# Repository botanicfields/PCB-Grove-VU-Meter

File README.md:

# PCB-Grove-VU-Meter
VU Meters into the Grove of M5

# オーディオレベルメーター用Grove(M5)接続基板
　ステレオオーディオ信号を、レベルメーター用のアナログ電圧信号に変換するプリント基板です。アナログ信号2本とM5Stack用の5V電源を、Groveコネクタから出力します。M5StackのLCDにVUメーターのように表示するサンプルプログラムを用意しています。

### サンプルプログラムの動作不良について
(2023/5/6) BF-037.inoは、以下の環境でコンパイルできました。しかしばがら、ADCによるオーディオ信号の取り込みが安定せず、使用に耐えない状況です。
- Arduino IDE 2.1.0
- Boards Manager:  
M5Stack by M5Stack official 2.0.7
- Library:  
M5Stack by M5Stack 0.4.3  
M5GFX 0.1.6

[内容物]  

動作例（YouTube）: [Audio level (VU/McIntosh) meters into the Grove of M5Stack](https://youtu.be/Pwd8X57_v_Q)

委託販売（スイッチサイエンス）:  [オーディオレベルメーター用Grove(M5)接続基板](https://www.switch-science.com/catalog/7947/)

## 安全上の注意事項
- 異常の場合、躊躇なくDCプラグを抜いてください（基板上のレギュレータ(U3)が触れないぐらい発熱しているなど）。その上で原因を取り除いてください。
- Groveへの5V出力は、必要な場合以外は、ジャンパピンJP3で切り離してください。特に電源が3.3Vの装置に5Vを供給すると焼損など事故の原因となります。
- 本基板からの5VとM5Stack側からの5Vは共存できません。僅かな電圧差から大電流が流れ、素子の発熱による火傷や、M5Stackの故障の原因になります。
- M5StackへのUSB-C以外の5V電源供給は推奨されていません。本基板の機能を含め、M5Stackへの直接の5V供給は自己責任です。

## 特徴
- オーディオ信号を整流し対数圧縮する専用LSI(ROHM BA6138)を使用しています。
- 基板上の半固定抵抗でフルスケールを調整できます。
- M5Stackの標準ボトムのピンソケットに接続するためのケーブルを添付しています。
- M5Stackへ5V電源を供給でき、スタンドアロン動作ができます。
- 左右2系統のRCAピンジャックが各々2個(In, Out)あり、RCAケーブルを中継できます。

## 注意事項
- 本基板は測定器ではありません。PCオーディオなどの手軽なオーディオ環境で見た目を楽しむための小物（ガジェット、ウィジェット、アクセサリ）です。サンプルプログラムの目盛も全くの飾りです。  
- BA6138は入力抵抗も2kΩ程度と低く、音質への影響は小さくないものと思われます。

## Groveコネクタへの5V電源供給のON/OFF
　本基板のジャンパピンJP3でGroveコネクタへの5V供給のON/OFFを設定します。JP3の切替は、DCプラグを抜いて実施ください。出荷時はOFFです。

| JP3 | Grove 5Vピン | M5Stackの電源 | 用途 |
|:-:|:- |:- |:- |
| OFF | 接続なし | USB-C、またはバッテリから供給(*1) | プログラム書き込み、シリアルモニターの利用など |
| ON  | 5Vを供給 | 本基板から供給(*2) | M5Stackをスタンドアロンで使用など |

(*1) JP3をOFFに設定してから、本基板のDCプラグを差し込んでください。  
(*2) JP3をONに設定する際は、USB-Cケーブルを取り外し、M5Stackを電源OFFとしてから、本基板のDCプラグを差し込んでください。バッテリ動作中のM5Stackは、電源/リセットボタンを2回押すことで電源OFFにできます。

[USB-C接続あり]  

[Groveから電源供給]  

## 仕様
- 外形寸法: 92x44mm
- 電源入力: DCジャック（DC 9V）
- 信号入力: RCAピンジャック（L/R, オーディオラインレベル）
- 信号出力: Groveコネクタ（アナログ2本）
- 電源出力: Groveコネクタ（DC 5V）

## 内容物
- プリント基板（完成品）
- Grove-4ピン-ジャンパオスケーブル [SEEED-110990210](https://www.switch-science.com/catalog/6245/)　※5本入のうちの１本です
- 説明書

## 使用方法
- 電源（ACアダプタ等）は添付しません。別途ご用意ください。  
例：秋月電子通商　スイッチングＡＣアダプター　９Ｖ１．３Ａ [AD-B90P130](https://akizukidenshi.com/catalog/g/gM-11998/)
- 電源スイッチはありません。入力や出力を接続し、設定を確かめてからDCプラグを差し込んでください。
- RCAジャックは2系統（赤・白）あり、各々2個が並列になっています。便宜上、基板シルクにはIN, OUTと表示しています。
- Groveの出力信号はアナログ電圧です。M5StackのPort A(I2C)には接続できません。M5Stackのボトムの端子に接続してください。

[サンプルプログラム使用時のM5Stackへの接続]  

|Grove|M5Stack|
|:-:|:-:|
|L  |GPIO35|
|R  |GPIO36|
|5V |5V |
|GND|GND|

- 基板上の半固定抵抗は、ご使用の環境で再調整ください。調整には小型のプラスドライバが必要です。

### 出荷時の調整の環境
- Windows11
- USB DAC: Sound Blaster Digital Music Premium HD(SB1240) [製品情報](https://jp.creative.com/p/sound-blaster/sound-blaster-digital-music-premium-hd)  
※安定動作のためには、Windows10 64bit用ドライバーの適用が有効な様です。[ドライバーダウンロード](https://jp.creative.com/support/downloads/download.asp?MainCategory=1091&nRegionFK=&nCountryFK=&nLanguageFK=&sOSName=&region=2&Product_Name=Sound+Blaster+Digital+Music+Premium+HD&Product_ID=19829&modelnumber=&driverlang=1041&OS=52&drivertype=0)
- YouTube Music: Audiolab 2014: Audio Test Tones: [1kHz 0dB](https://music.youtube.com/watch?v=_XMpb9BjGgE&feature=share)
- VUメーターが-5VUを示す様に調整（一般音源のメーターの振れが適当になる位置）

[入力信号-3dB(L/R)に対する出力(L/R)の例]  

[音楽信号入力(L/R)に対する出力(L/R)の例]  

## ご参考
- ROHM BA6138  
aitendo扱い レベルメーターアンプ [BA6138](https://www.aitendo.com/product/11726)
データシート[BA6138](http://aitendo3.sakura.ne.jp/aitendo_data/product_img/ic/audio/BA6138/BA6138.pdf)
- 基板上の、以下の部品等は未使用です。  
J5, J6, J9（短絡済）, JP1, JP2, R5, R6

[基板裏面]

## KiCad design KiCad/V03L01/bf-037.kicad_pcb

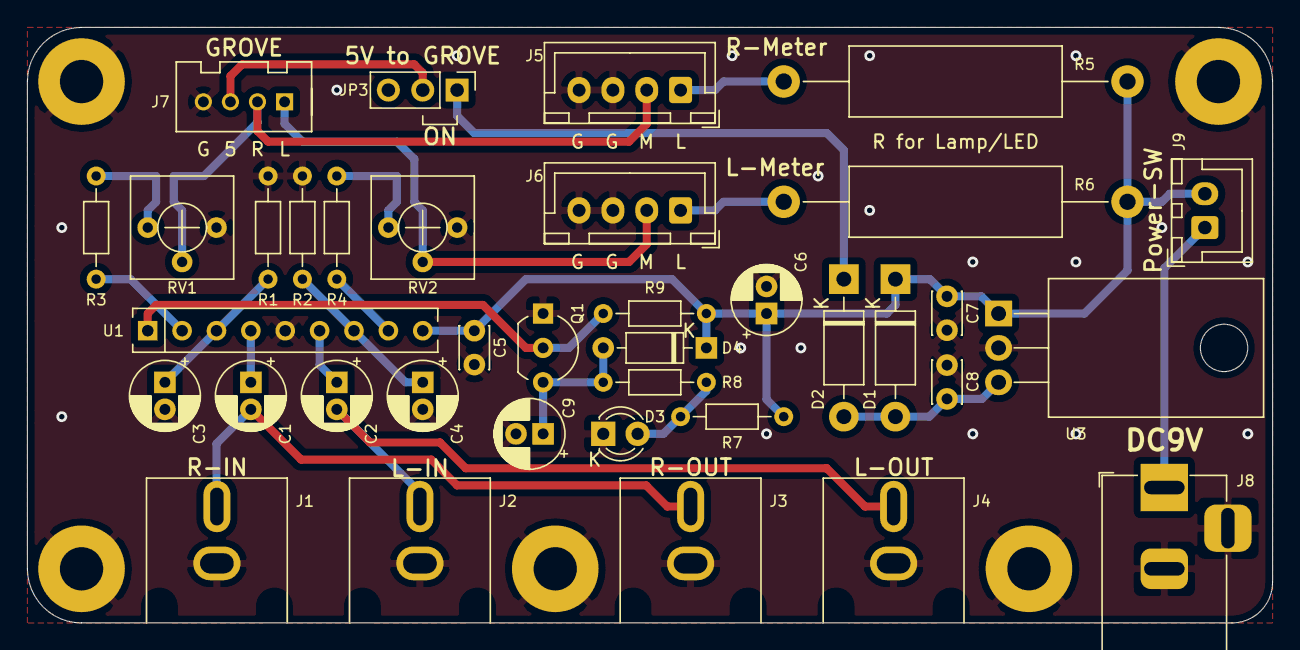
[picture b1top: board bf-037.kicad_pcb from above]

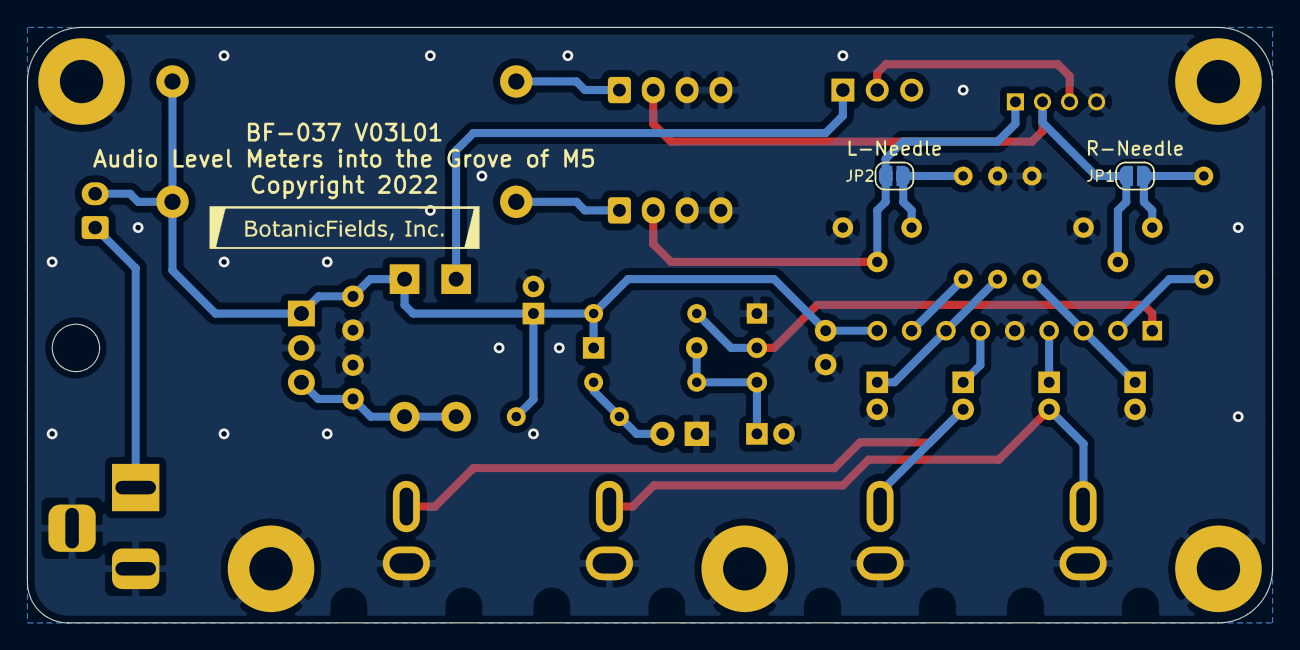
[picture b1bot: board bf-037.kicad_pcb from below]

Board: 2 copper layers, 92.0 x 44.0 mm, 39 parts (2 on the bottom side), 23 nets.

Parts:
C1, C2, C3, C4: 4.7u; CP_Radial_D5.0mm_P2.00mm
C5, C8: 100n; C_Disc_D3.0mm_W2.0mm_P2.50mm
C6, C9: 100u; CP_Radial_D5.0mm_P2.00mm
C7: 330n; C_Disc_D3.0mm_W2.0mm_P2.50mm
D1: 1N4001; D_DO-41_SOD81_P10.16mm_Horizontal
D2: SB240LES; D_DO-41_SOD81_P10.16mm_Horizontal
D3: LED; LED_D3.0mm
D4: IN4148; D_DO-35_SOD27_P7.62mm_Horizontal
J1: R-IN; BF@RCA-2P-XINA
J2: L-IN; BF@RCA-2P-XINA
J3: R-OUT; BF@RCA-2P-XINA
J4: L-OUT; BF@RCA-2P-XINA
J5: R-Meter; JST_XH_B4B-XH-A_1x04_P2.50mm_Vertical
J6: L-Meter; JST_XH_B4B-XH-A_1x04_P2.50mm_Vertical
J7: Grove-Analog; HW4-2.0
J8: 9V; BF@BarrelJack_Horizontal
J9: PowerSW; JST_XH_B2B-XH-A_1x02_P2.50mm_Vertical
JP1: R-Needle; SolderJumper-2_P1.3mm_Open_RoundedPad1.0x1.5mm
JP2: L-Needle; SolderJumper-2_P1.3mm_Open_RoundedPad1.0x1.5mm
JP3: 5V to GROVE; PinHeader_1x03_P2.54mm_Vertical
Q1: 2SC1815; TO-92_Inline_Wide
R1, R2: 330k; R_Axial_DIN0204_L3.6mm_D1.6mm_P7.62mm_Horizontal
R3, R4: 1k; R_Axial_DIN0204_L3.6mm_D1.6mm_P7.62mm_Horizontal
R5, R6: 1.5k; R_Axial_DIN0516_L15.5mm_D5.0mm_P25.40mm_Horizontal
R7: 6.8k; R_Axial_DIN0204_L3.6mm_D1.6mm_P7.62mm_Horizontal
R8: 47k; R_Axial_DIN0204_L3.6mm_D1.6mm_P7.62mm_Horizontal
R9: 10k; R_Axial_DIN0204_L3.6mm_D1.6mm_P7.62mm_Horizontal
RV1, RV2: 10kB; BF@BOURNS3362P
U1: BA6138; SIP-9_22.3x3mm_P2.54mm
U3: LM7805_TO220; TO-220-3_Horizontal_TabDown

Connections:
+5V: C8.1, D1.2, D2.2, U3.3
GND: C3.2, C4.2, C5.2, C6.2, C7.2, C8.2, C9.2, D3.1, J1.2, J2.2, J3.2, J4.2, J5.3, J5.4, J6.3, J6.4, J7.4, J8.2, J8.3, Q1.1, R1.2, R2.2, RV1.1, RV2.1, U1.5, U3.2
unnamed: C1.1, U1.4
unnamed: C1.2, J1.1, J3.1
unnamed: C2.1, U1.6
unnamed: C2.2, J2.1, J4.1
unnamed: C3.1, R1.1, U1.3
unnamed: C4.1, R2.1, U1.7
unnamed: C9.1, D4.2, Q1.3, R8.2
unnamed: D2.1, JP3.1
unnamed: D3.2, R7.2, R8.1
unnamed: J5.1, R5.1
unnamed: J5.2, J7.2, JP1.2, RV1.2
unnamed: J6.1, R6.1
unnamed: J6.2, J7.1, JP2.2, RV2.2
unnamed: J7.3, JP3.2
unnamed: J8.1, J9.1
unnamed: JP1.1, R3.1, RV1.3
unnamed: JP2.1, R4.1, RV2.3
unnamed: Q1.2, R9.2, U1.1
unnamed: R3.2, U1.2
unnamed: R4.2, U1.8
VCC: C5.1, C6.1, C7.1, D1.1, D4.1, J9.2, R5.2, R6.2, R7.1, R9.1, U1.9, U3.1

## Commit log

2022-02-11 first upload
    first upload
2022-02-11 Update README.md
    refine description
2022-02-12 add doc
    add bf-037_doc.pdf
2022-02-19 doc, readme
    refine description
2023-05-01 BF-037.ino
    removed: adc_gpio_init()
2023-05-06 BF-037
    updated to M5GFX 0.1.6

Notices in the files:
KiCad/V03L01/bf-037.kicad_pcb:
Copyright 2022 BotanicFeilds, Inc.
